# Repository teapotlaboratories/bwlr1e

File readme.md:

# Teapotlabs BWLR1E

Teapotlabs BWLR1E is a solar-powered wireless LoRa environmental sensor capable of sensing temperature, humidity, air pressure and air quality using the on-board BME688. 
With STM32WLE MCU as it's core and AEM10941 for solar charging, the device is capable of multi-year operation with the possibility of indefinite battery-life by utilizing the solar charging capability

Teapotlabs BWLR1E is part of  [Teapot open-hardware project](https://github.com/teapotlaboratories). 
  
## Disclaimer
- The 1KM range is based on [AERQ - Air Quality Monitoring](https://www.seeedstudio.com/blog/2022/04/27/monitoring-indoor-air-pollutants-the-silent-issue-for-smart-city-iot-using-seeed-lora-e5-and-fusion-pcba/) design, but have not been tested on this device yet

## Acknowledgement
The project won't be possible without the amazing work from people across the globe. The following are the reference to those awesome projects:

 - [LoRa e5 Tiny](https://github.com/hallard/LoRa-E5-Tiny)
 - [AERQ - Air Quality Monitoring](https://www.seeedstudio.com/blog/2022/04/27/monitoring-indoor-air-pollutants-the-silent-issue-for-smart-city-iot-using-seeed-lora-e5-and-fusion-pcba/)
	 - [Github](https://github.com/Mircerson/AERQ) 
 - [TSEM](https://hackaday.io/project/159139-tiny-solar-energy-module-tsem)

## Specification

- [RAK3172](https://docs.rakwireless.com/Product-Categories/WisDuo/RAK3172-Module/Overview/): An STM32WLE5CC module
- [AEM10941](https://e-peas.com/product/aem10941): Solar energy harvesting
- 3.3V only power/pin. 
- 3uA Deep-Sleep
- BME688 for Environmental Sensing
- Switchable TX Power. 14 dBm(50mA) or 22 dBm(140mA) ( on 915MHz frequency )
- Supports LoRaWAN 1.0.3
- 1KM+ Range
- UART2 breakout for **Arduino/Mbed OS/STM32Cube** programming 
- SWD breakout for debugging and programming
- iPEX antenna connector 
- 3.7 Volts LiPo Battery

## Schematics

## Boards
 <p align="center">  <br><b>PCB Render</b></p>

Built using KiCAD, the board is design to be as small as possible with all components placed on the top side of the PCB.
The following are the lists of revision of the board:
- Revision 1: Initial design
- Revision 2: Better trace, use rounded trace and change solar cell wiring to parallel for all cell
- Revision 3: Rename 3V3 to PRIMIN and breaks out PRIMIN
- Revision 4: Improve layout and wiring, and add Qwiic connector
- Revision 5: Change C6 to 22uF

The following design are based on the latest revision.
| Top Board | Bottom Board |
|--|--|
|  |  |
|  |  |

 <p align="center"> <br><b>PCB Top and Bottom Layout</b></p> 
  
### Case

Built using [TinkerCAD](https://www.tinkercad.com). The case are 3D printable with any generic 3D printer with/without support. The STL files are available [here](https://github.com/teapotlaboratories/bwlr1e/tree/main/hardware/main/case)
 <p align="center"><br><b>Case Open</b></p>

For adding additional sensors, Qwiic connector is also available on the left side of the board.
 <p align="center"><br><b>Connecting to Adafruit BME688</b></p>

The case is design to be as small as possible with an additional magnets in the back to ease the placement of the sensor. The following are the list of material used at the time of testing:
- 3.7v LiPo Battery, 850mAh 6mm x 30mm x 48mm
- 4 piece of 8mm x 2mm neodymium magnet

<p align="center"><br><b>Sensor Placement with Magnet</b></p>

### Measurement
Power consumption and solar charging current are measured using [Nordic PPK2](https://www.nordicsemi.com/Products/Development-hardware/Power-Profiler-Kit-2)  and [CurrentRanger](https://lowpowerlab.com/shop/product/152).
The following are the summary of the measurement:
- Transmit 14dBm:  305ms @ 20mA
- Deep-Sleep : 3.22 uA
- Direct Sunlight Solar Charge: 9mA
- Indirect Sunlight Solar Charge: 300uA

> :warning: **Tested on Revision 3, but should be similar to Revision 5** 

<p align="center"><br><b>Deep-Sleep</b></p>

<p align="center"><br><b>BME688 Measure and LoRa Transmit</b></p>

| Solar Charge - Direct Sunlight | Solar Charge - Indirect Sunlight |
|--|--|
|  |  |

More measurement can be found [here](https://github.com/teapotlaboratories/bwlr1e/tree/main/docs/measurement)

### Bill Of Materials
Most of the components are generic and can be bought from any electornics/semi-conductor distributor. RAK3172 is the only component available in [RAKwireless store](https://store.rakwireless.com/products/wisduo-lpwan-module-rak3172?variant=40014759493830). The bill of materials can be downloaded [here](https://github.com/teapotlaboratories/bwlr1e/blob/main/hardware/main/bill_of_materials.csv)

> :warning: **Be sure to buy the RAK3172 variant without IPEX to use the On-Board Antenna** 

## Programming

> :warning: **Board can only be powered when LiPo battery is connected** 

Programming the device can be done over the **UART2** or **SWD**, available on the right side of the board or uses the [BWLR1E Programmer](https://github.com/teapotlaboratories/bwlr1e/blob/main/readme_programmer.md).
Out of the factory, the RAK3172 chip ships with an **AT firmware** that can be tested by connecting a USB-to-UART bridge to the **UART2** port.

The following are some very good tutorial to start developing with the device:

- [Communicating with the AT firmware](https://docs.rakwireless.com/Product-Categories/WisDuo/RAK3172-Module/Quickstart/#rak3172-as-a-lora-lorawan-modem-via-at-command)
 - [Programming with Arduino](https://docs.rakwireless.com/Product-Categories/WisDuo/RAK3172-Module/Quickstart/#rak3172-as-a-stand-alone-device-using-rui3)
 - [Programming with STM32Cube](https://docs.rakwireless.com/Product-Categories/WisDuo/RAK3172-Module/Low-Level-Development/#rak3172-on-stm32cubeide-with-stm32wl-sdk-v1-0-0)
 - [Programming with MbedOS](https://github.com/hallard/LoRa-E5-Tiny/blob/main/README.md#compile-and-flash-firmware)

For connecting to the **UART2** port, use any USB-to-UART bridge module. In testing, the [Sparkfun](https://www.sparkfun.com/products/14050) board is used for communication with AT firmware and programming over **Arduino**.
 <p align="center"> <br>Sparkfun USB-to-UART Bridge</p>

> :warning: **Be sure to only use 3.3V module. Do not 5V module** 

### Available SDK
Through **UART2**, user can program the device using the following SDK:
- [Arduino RUI3 SDK](https://github.com/RAKWireless/RAKwireless-Arduino-BSP-Index)
- [Arduino STM32duino SDK](https://github.com/stm32duino/Arduino_Core_STM32)
- [MbedOS](https://github.com/hallard/LoRa-E5-Tiny/blob/main/README.md#compile-and-flash-firmware)
- [STM32Cube](https://docs.rakwireless.com/Product-Categories/WisDuo/RAK3172-Module/Low-Level-Development/#installation-of-stm32cube-ide)

Other than [Arduino RUI3 SDK](https://github.com/RAKWireless/RAKwireless-Arduino-BSP-Index), to program the device, user need to put the device in Serial Bootloader mode by,
1. Press and Hold `BOOT` and `RESET` button
2. Release `RESET` button 
3. Wait few seconds ( try 2 seconds )
4. Release `BOOT` button
5. Device should be in Serial Bootloader mode.

You can also use [STM32CubeProgrammer](https://www.st.com/en/development-tools/stm32cubeprog.html) , instead of the SDK  to upload a firmware
  
### Programming with Teapotlabs BWLR1E Programmer
 <p align="center"> <br>Teapotlabs BWLR1E Programmer</p>

An alternative to solder-free programming is to use the Teapotlabs BWLR1E Programmer. A full detail of the device can be found [here](https://github.com/teapotlaboratories/bwlr1e/blob/main/readme_programmer.md).
The programmer connects to UART2 of the device. 

## License
The product is open-source! However, some part of library used under **src**, might have it's own license.
Please reach out or create a ticket to report any license violation.

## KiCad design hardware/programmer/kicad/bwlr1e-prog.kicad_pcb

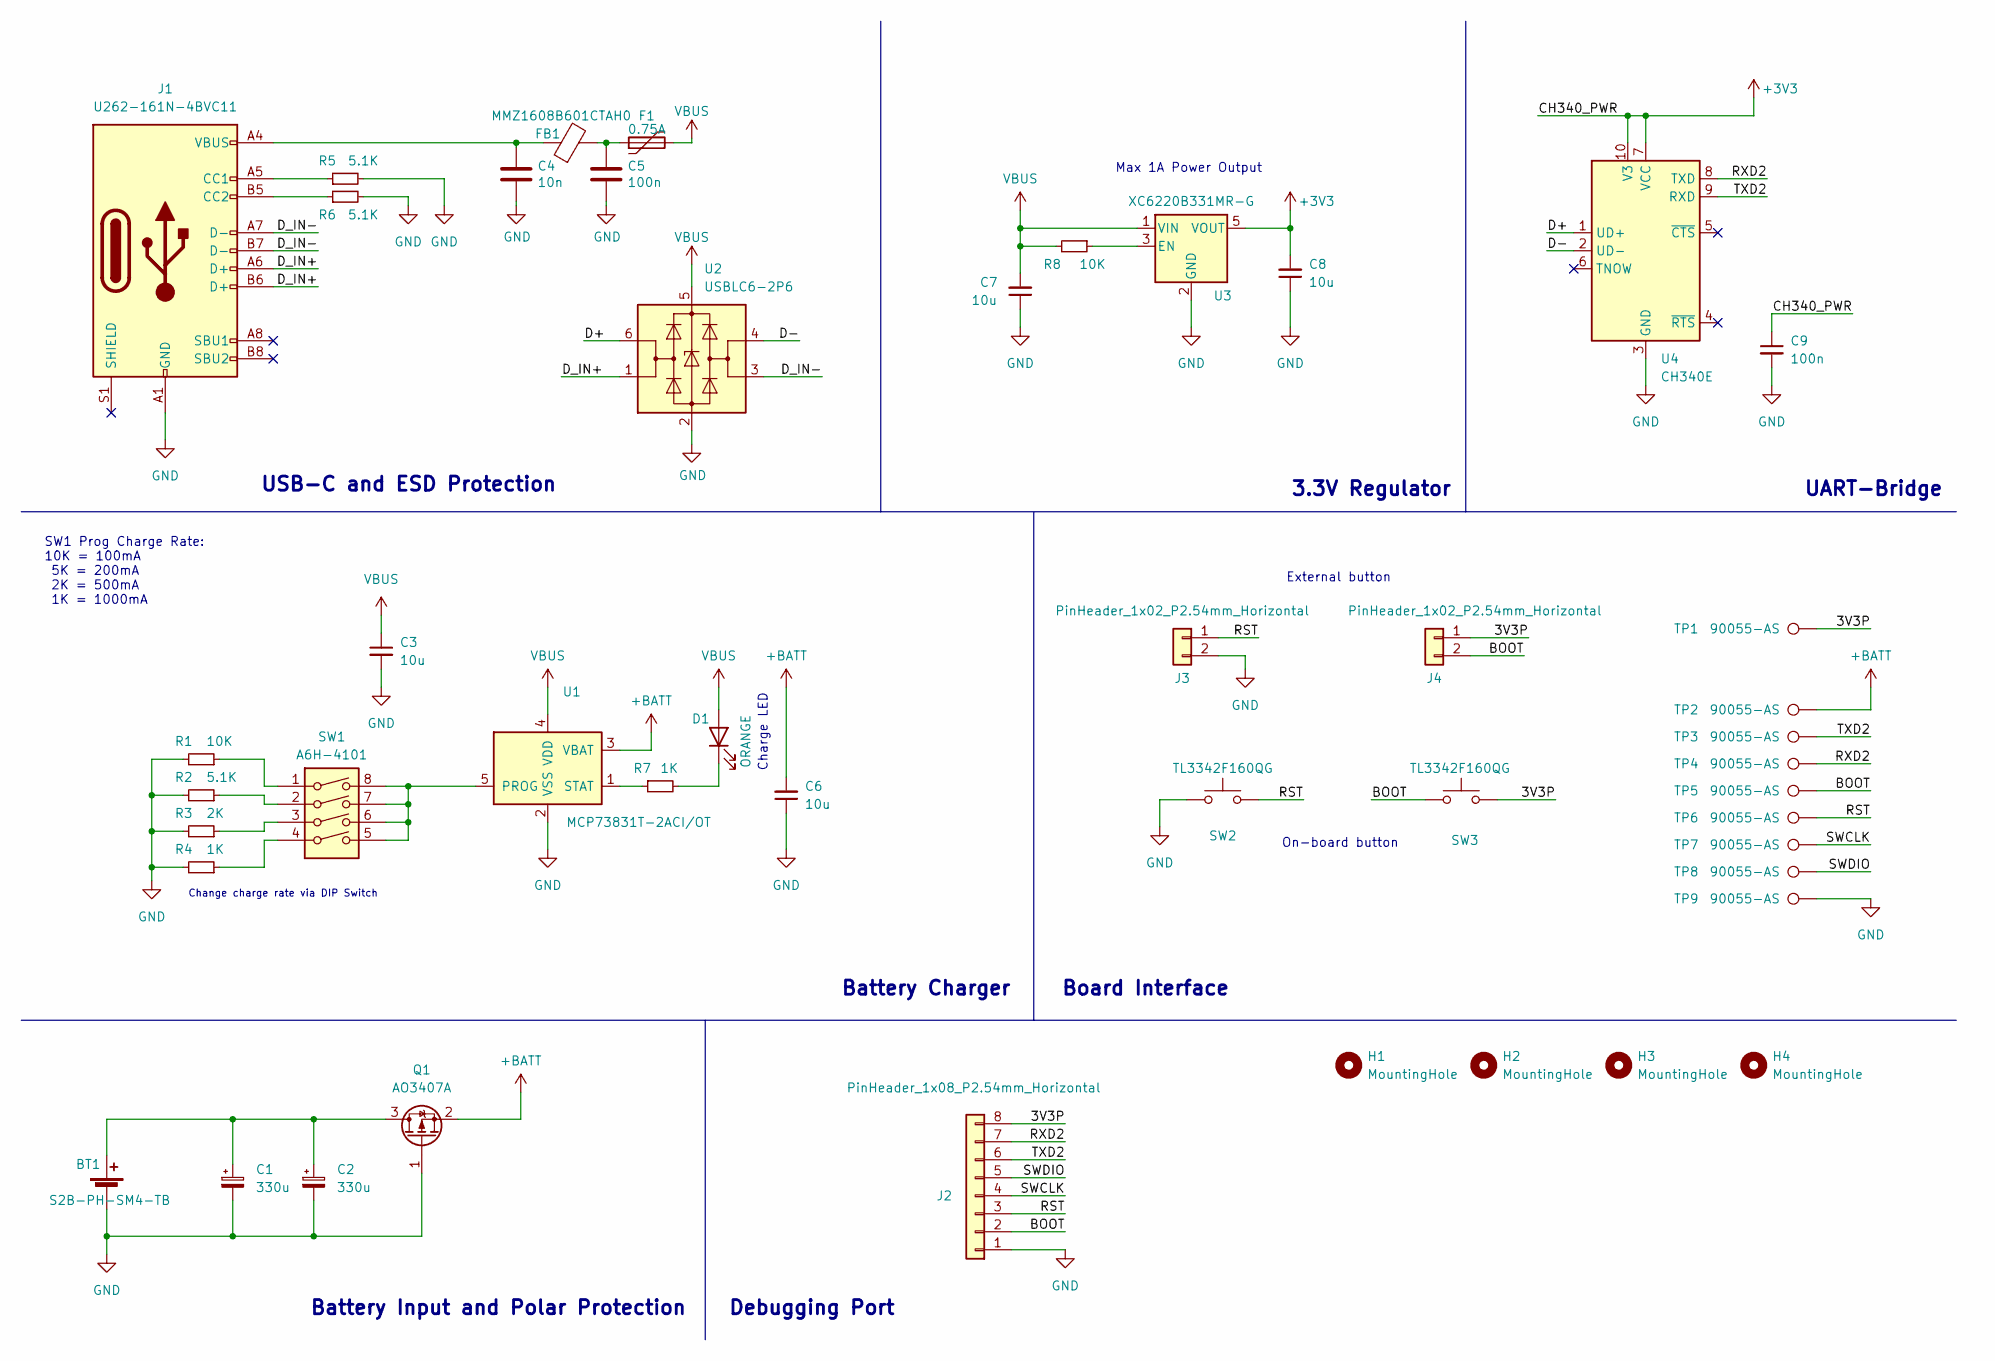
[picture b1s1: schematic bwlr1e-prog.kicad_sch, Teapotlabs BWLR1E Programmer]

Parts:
BT1: S2B-PH-SM4-TB; JST_PH_S2B-PH-SM4-TB_1x02-1MP_P2.00mm_Horizontal; Part Number S2B-PH-SM4-TB
C1, C2: 330u; CP_EIA-3528-15_AVX-H; Part Number T520B337M006ATE040
C3: 10u; C_0603_1608Metric; Part Description Ceramic Capacitor 10uF 10% 10V X5R
C4: 10n; C_0402_1005Metric; Part Number CC0402KRX7R9BB103
C5: 100n; C_0402_1005Metric; Part Number CC0402KRX5R6BB104
C6, C7, C8: 10u; C_0805_2012Metric; Part Description Ceramic Capacitor 10uF 10% 10V X5R
C9: 100n; C_0603_1608Metric; Part Description Ceramic Capacitor 100nF 10% 10V X7R
D1: ORANGE; LED_0603_1608Metric; Part Description Orange 2V 25mA
F1: 0.75A; Fuse_0805_2012Metric; Part Number SMD0805P075TF
FB1: MMZ1608B601CTAH0; L_0603_1608Metric; Part Number MMZ1608B601CTAH0
H1, H2, H3, H4: MountingHole; MountingHole_2.2mm_M2
J1: U262-161N-4BVC11; USB_C_Receptacle_XKB_U262-16XN-4BVC11; Part Number U262-161N-4BVC11
J2: PinHeader_1x08_P2.54mm_Horizontal
J3, J4: PinHeader_1x02_P2.54mm_Horizontal
Q1: AO3407A; SOT-23; Part Number AO3407A
R1: 10K; R_0603_1608Metric; Part Description Resistor 10K 1% 100mW
R2: 5.1K; R_0603_1608Metric; Part Description Resistor 5.1K 1% 100mW
R3: 2K; R_0603_1608Metric; Part Description Resistor 2K 1% 100mW
R4: 1K; R_0603_1608Metric; Part Description Resistor 1K 1% 100mW
R5, R6: 5.1K; R_0402_1005Metric; Part Description Resistor 5.1K 1% 62.5mW
R7: 1K; R_0603_1608Metric; Part Description Resistor 1k 5% 100mW
R8: 10K; R_0603_1608Metric; Part Description Resistor 10k 5% 100mW
SW1: A6H-4101; SW_DIP_SPSTx04_Slide_Omron_A6H-4101_W6.15mm_P1.27mm; Part Number A6H-4101
SW2, SW3: TL3342F160QG; SW_SPST_TL3342; Part Number TL3342F160QG
TP1, TP2, TP3, TP4, TP5, TP6, TP7, TP8, TP9: 90055-AS; Part Number 90055-AS
U1: MCP73831T-2ACI/OT; SOT-23-5; Part Number MCP73831T-2ACI/OT
U2: USBLC6-2P6; SOT-666; Part Number USBLC6-2P6
U3: XC6220B331MR-G; SOT-23-5; Part Number XC6220B331MR-G
U4: CH340E; MSOP-10_3x3mm_P0.5mm; Part Number CH340E

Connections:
+3V3: C8.2, C9.1, U3.5 (VOUT), U4.7 (VCC), U4.10 (V3)
+BATT: C6.2, Q1.2 (S), TP2.1, U1.3 (VBAT)
/3V3P: J2.8, J4.1, SW3.2, TP1.1
/BOOT: J2.2, J4.2, SW3.1, TP5.1
/D+: U2.6 (I/O1), U4.1 (UD+)
/D-: U2.4 (I/O2), U4.2 (UD-)
/D_IN+: J1.A6 (D+), J1.B6 (D+), U2.1 (I/O1)
/D_IN-: J1.A7 (D-), J1.B7 (D-), U2.3 (I/O2)
/RST: J2.3, J3.1, SW2.2, TP6.1
/RXD2: J2.7, TP4.1, U4.8 (TXD)
/SWCLK: J2.4, TP7.1
/SWDIO: J2.5, TP8.1
/TXD2: J2.6, TP3.1, U4.9 (RXD)
GND: BT1.2 (-), C1.2, C2.2, C3.2, C4.2, C5.2, C6.1, C7.1, C8.1, C9.2, J1.A1 (GND), J1.A12 (GND), J1.B1 (GND), J1.B12 (GND), J2.1, J3.2, Q1.1 (G), R1.2, R2.2, R3.2, R4.2, R5.2, R6.2, SW2.1, TP9.1, U1.2 (VSS), U2.2 (GND), U3.2 (GND), U4.3 (GND)
unnamed: BT1.1 (+), C1.1, C2.1, Q1.3 (D)
unnamed: C4.1, FB1.1, J1.A4 (VBUS), J1.A9 (VBUS), J1.B4 (VBUS), J1.B9 (VBUS)
unnamed: C5.1, F1.1, FB1.2
unnamed: D1.1 (K), R7.2
unnamed: J1.A5 (CC1), R5.1
unnamed: J1.B5 (CC2), R6.1
unnamed: R1.1, SW1.1
unnamed: R2.1, SW1.2
unnamed: R3.1, SW1.3
unnamed: R4.1, SW1.4
unnamed: SW1.5, SW1.6, SW1.7, SW1.8, U1.5 (PROG)
unnamed: R7.1, U1.1 (STAT)
unnamed: R8.1, U3.3 (EN)
VBUS: C3.1, C7.2, D1.2 (A), F1.2, R8.2, U1.4 (VDD), U2.5 (VBUS), U3.1 (VIN)

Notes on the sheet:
SW1 Prog Charge Rate: 10K = 100mA 5K = 200mA 2K = 500mA 1K = 1000mA
External button
Max 1A Power Output
On-board button
Debugging Port
Charge LED
UART-Bridge
Change charge rate via DIP Switch
Battery Input and Polar Protection
USB-C and ESD Protection
Battery Charger
3.3V Regulator
Board Interface

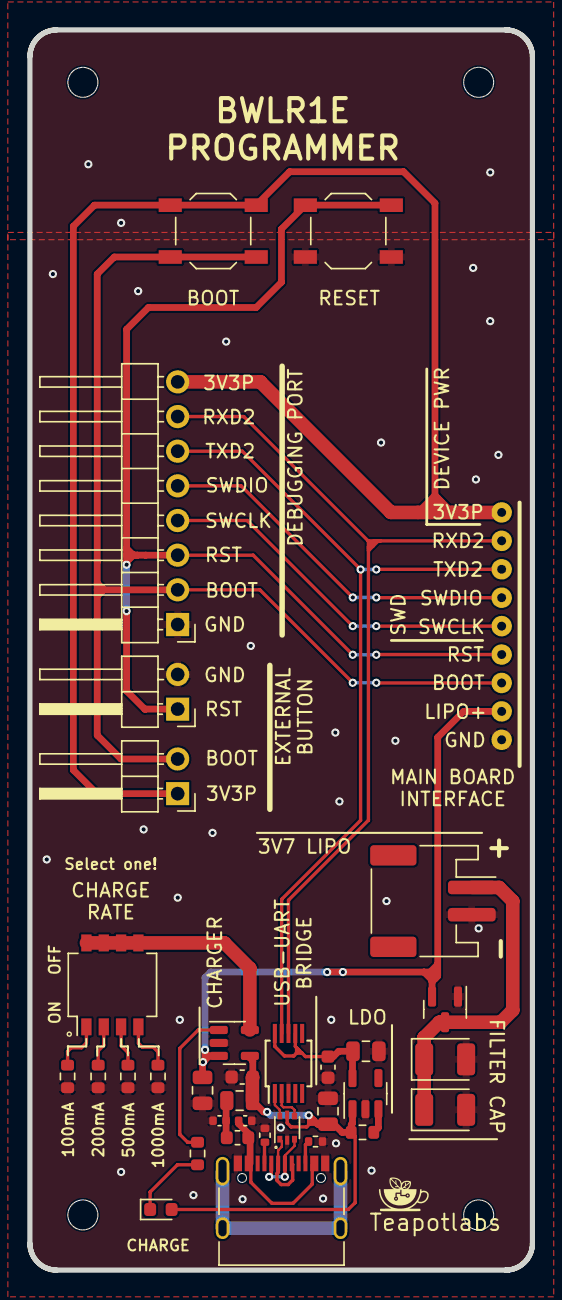
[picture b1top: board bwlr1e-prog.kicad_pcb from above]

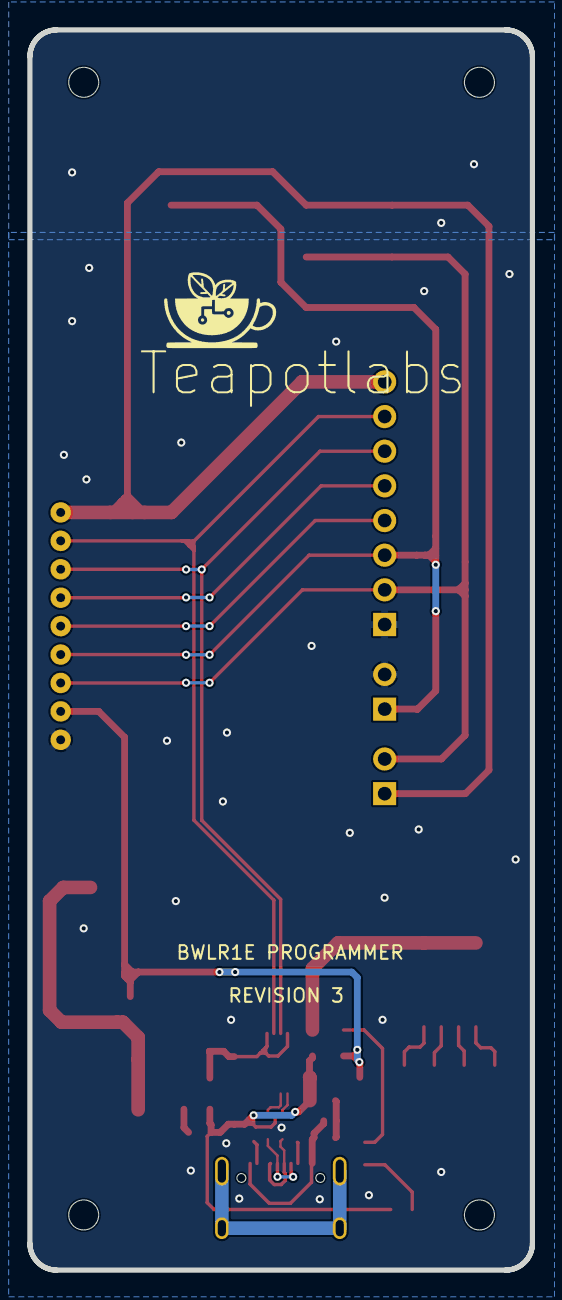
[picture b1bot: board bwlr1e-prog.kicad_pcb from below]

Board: 2 copper layers, 36.8 x 90.9 mm, 46 parts (9 on the bottom side), 28 nets.

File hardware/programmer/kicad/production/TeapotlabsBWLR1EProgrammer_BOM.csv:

Id,Designator,Quantity,Manufacturer,Manufacturer Part Number,Value,Description,Footprint,Type,Distributor,Distributor Part Number,Distributor Link
1,BT1,1,JST,S2B-PH-SM4-TB(LF)(SN),S2B-PH-SM4-TB(LF)(SN),"Connector Header Right Angle 2 position 0.079"" (2.00mm)",JST_PH_S2B-PH-SM4-TB,SMD,LCSC,C295747,https://www.lcsc.com/product-detail/Wire-To-Board-Wire-To-Wi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
2,"C1, C2",2,KEMET,T520B337M006ATE040,330u,Tantalum Capacitors 330µF 20% 6.3 V 40mOhm,CP_EIA-3528-15_AVX-H,SMD,LCSC,C696806,https://www.lcsc.com/product-detail/span-style-background-co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
3,C3,1,Samsung Electro-Mechanics,CL10A106KP8NNNC,10u,Ceramic Capacitor 10uF 10% 10V X5R,0603_1608Metric,SMD,LCSC,C19702,https://www.lcsc.com/product-detail/_Samsung-Electro-Mechani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
4,C4,1,YAGEO,CC0402KRX7R9BB103,10n,Ceramic Capacitor 10nF 10% 50V X7R,0402_1005Metric,SMD,LCSC,C60133,https://www.lcsc.com/product-detail/Multilayer-Ceramic-Capac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
5,C5,1,YAGEO,CC0402KRX5R6BB104,100n,Ceramic Capacitor 100nF 10% 10V X5R,0402_1005Metric,SMD,LCSC,C129131,https://www.lcsc.com/product-detail/Multilayer-Ceramic-Capac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
6,"C6, C7, C8",3,Samsung Electro-Mechanics,CL21A106KPFNNNE,10u,Ceramic Capacitor 10uF 10% 10V X5R,0805_2012Metric,SMD,LCSC,C17024,https://www.lcsc.com/product-detail/_Samsung-Electro-Mechani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
7,C9,1,YAGEO,CC0603KRX7R6BB104,100n,Ceramic Capacitor 100nF 10% 10V X7R,0603_1608Metric,SMD,LCSC,C519438,https://www.lcsc.com/product-detail/_YAGEO-_C519438.html
8,D1,1,EKINGLUX,E6C0603SEAC1UDA,ORANGE,LED Orange 2V 25mA,0603_1608Metric,SMD,LCSC,C375450,https://www.lcsc.com/product-detail/_EKINGLUX-_C375450.html
9,F1,1,RUILON,SMD0805P075TF,0.75A,Resettable Fuses 6V 750mA 40A 1.5A,0805_2012Metric,SMD,LCSC,C20979,https://www.lcsc.com/product-detail/Resettable-Fuses_RUILON-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
10,FB1,1,TDK,MMZ1608B601CTAH0,MMZ1608B601CTAH0,Ferrite Beads 400mΩ ±25% 600Ω@100MHz,0603_1608Metric,SMD,LCSC,C97120,https://www.lcsc.com/product-detail/Ferrite-Beads_TDK-MMZ160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
12,J1,1,XKB Connectivity,U262-161N-4BVC11,U262-161N-4BVC11,USB-C Receptacle,XKB_U262-16XN-4BVC11,SMD,LCSC,C319148,https://www.lcsc.com/product-detail/USB-Connectors_XKB-Conne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
13,J2,1,HCTL,PZ254-1-08-W-8.5,PinHeader_1x08_P2.54mm_Horizontal,PinHeader 1x08 Pitch 2.54mm Horizontal,PinHeader_1x08_P2.54mm_Horizontal,THT,LCSC,C2894950,https://www.lcsc.com/product-detail/span-style-background-co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
14,"J3, J4",2,XFCN,PZ254R-11-02P,PinHeader_1x02_P2.54mm_Horizontal,PinHeader 1x02 Pitch 2.54mm Horizontal,PinHeader_1x02_P2.54mm_Horizontal,THT,LCSC,C492410,https://www.lcsc.com/product-detail/span-style-background-co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
15,Q1,1,Alpha & Omega Semicon,AO3407A,AO3407A,"MOSFET P Channel 30V 4.3A 48mΩ@10V,4.3A 1.4W",SOT-23,SMD,LCSC,C15155,https://www.lcsc.com/product-detail/MOSFETs_Alpha-Omega-Semi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
16,"R1, R8",2,UNI-ROYAL(Uniroyal Elec),0603WAF1002T5E,10K,Resistor 10K 1% 100mW,0603_1608Metric,SMD,LCSC,C25804,https://www.lcsc.com/product-detail/Chip-span-style-backgrou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
17,R2,1,UNI-ROYAL(Uniroyal Elec),0603WAF5101T5E,5.1K,Resistor 5.1K 1% 100mW,0603_1608Metric,SMD,LCSC,C23186,https://www.lcsc.com/product-detail/Chip-span-style-backgrou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
18,R3,1,UNI-ROYAL(Uniroyal Elec),0603WAF2001T5E,2K,Resistor 2K 1% 100mW,0603_1608Metric,SMD,LCSC,C22975,https://www.lcsc.com/product-detail/Chip-span-style-backgrou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
19,"R4, R7",2,UNI-ROYAL(Uniroyal Elec),0603WAF1001T5E,1K,Resistor 1K 1% 100mW,0603_1608Metric,SMD,LCSC,C21190,https://www.lcsc.com/product-detail/Chip-span-style-backgrou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
20,"R5, R6",2,UNI-ROYAL(Uniroyal Elec),0402WGF5101TCE,5.1K,Resistor 5.1K 1% 100mW,0402_1005Metric,SMD,LCSC,C25905,https://www.lcsc.com/product-detail/Chip-span-style-backgrou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
21,SW1,1,Omron,A6H-4101,A6H-4101,DIP Switches SMD 4Bit SPST 24V 25mA,A6H-4101,SMD,LCSC,C397291,https://www.lcsc.com/product-detail/DIP-Switches_Omron-Elect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
22,"SW2, SW3",2,E-Switch,TL3342F160QG,TL3342F160QG,SPST SMD NO 50mA 100MΩ 100000 Times 12V 160gf@±50gf,SW_SPST_TL3342,SMD,LCSC,C2886898,https://www.lcsc.com/product-detail/Tactile-Switches_E-Switc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
23,"TP1, TP2, TP3, TP4, TP5, TP6, TP7, TP8, TP9",9,Preci-Dip,90055-AS,90055-AS,Contact Spring Loaded SMD Gold,90055-AS,THT,Digikey,1212-1855-ND,https://www.digikey.com/en/products/detail/preci-dip/90055-A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
24,U1,1,Microchip,MCP73831T-2ACI/OT,MCP73831T-2ACI/OT, Battery Management ICs 1.5A,SOT-23-5,SMD,LCSC,C424093,https://www.lcsc.com/product-detail/Battery-Management-ICs_M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
25,U2,1,STMicroelectronics,USBLC6-2P6,USBLC6-2P6, ESD Protection Devices 6V 17V Unidirectional 5.25V,SOT-666,SMD,LCSC,C15999,https://www.lcsc.com/product-detail/ESD-Protection-Devices_S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
26,U3,1,Torex Semiconductor,XC6220B331MR-G,XC6220B331MR-G,Linear Voltage Regulators (LDO) 1000mA Fixed +3.3V,SOT-23-5,SMD,LCSC,C86534,https://www.lcsc.com/product-detail/Linear-Voltage-Regulator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
27,U4,1,WCH,CH340E,CH340E,USB-UART Bridge 2Mbps Transceiver USB 2.0,MSOP-10_3x3mm_P0.5mm,SMD,LCSC,C99652,https://www.lcsc.com/product-detail/USB-ICs_WCH-Jiangsu-Qin-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

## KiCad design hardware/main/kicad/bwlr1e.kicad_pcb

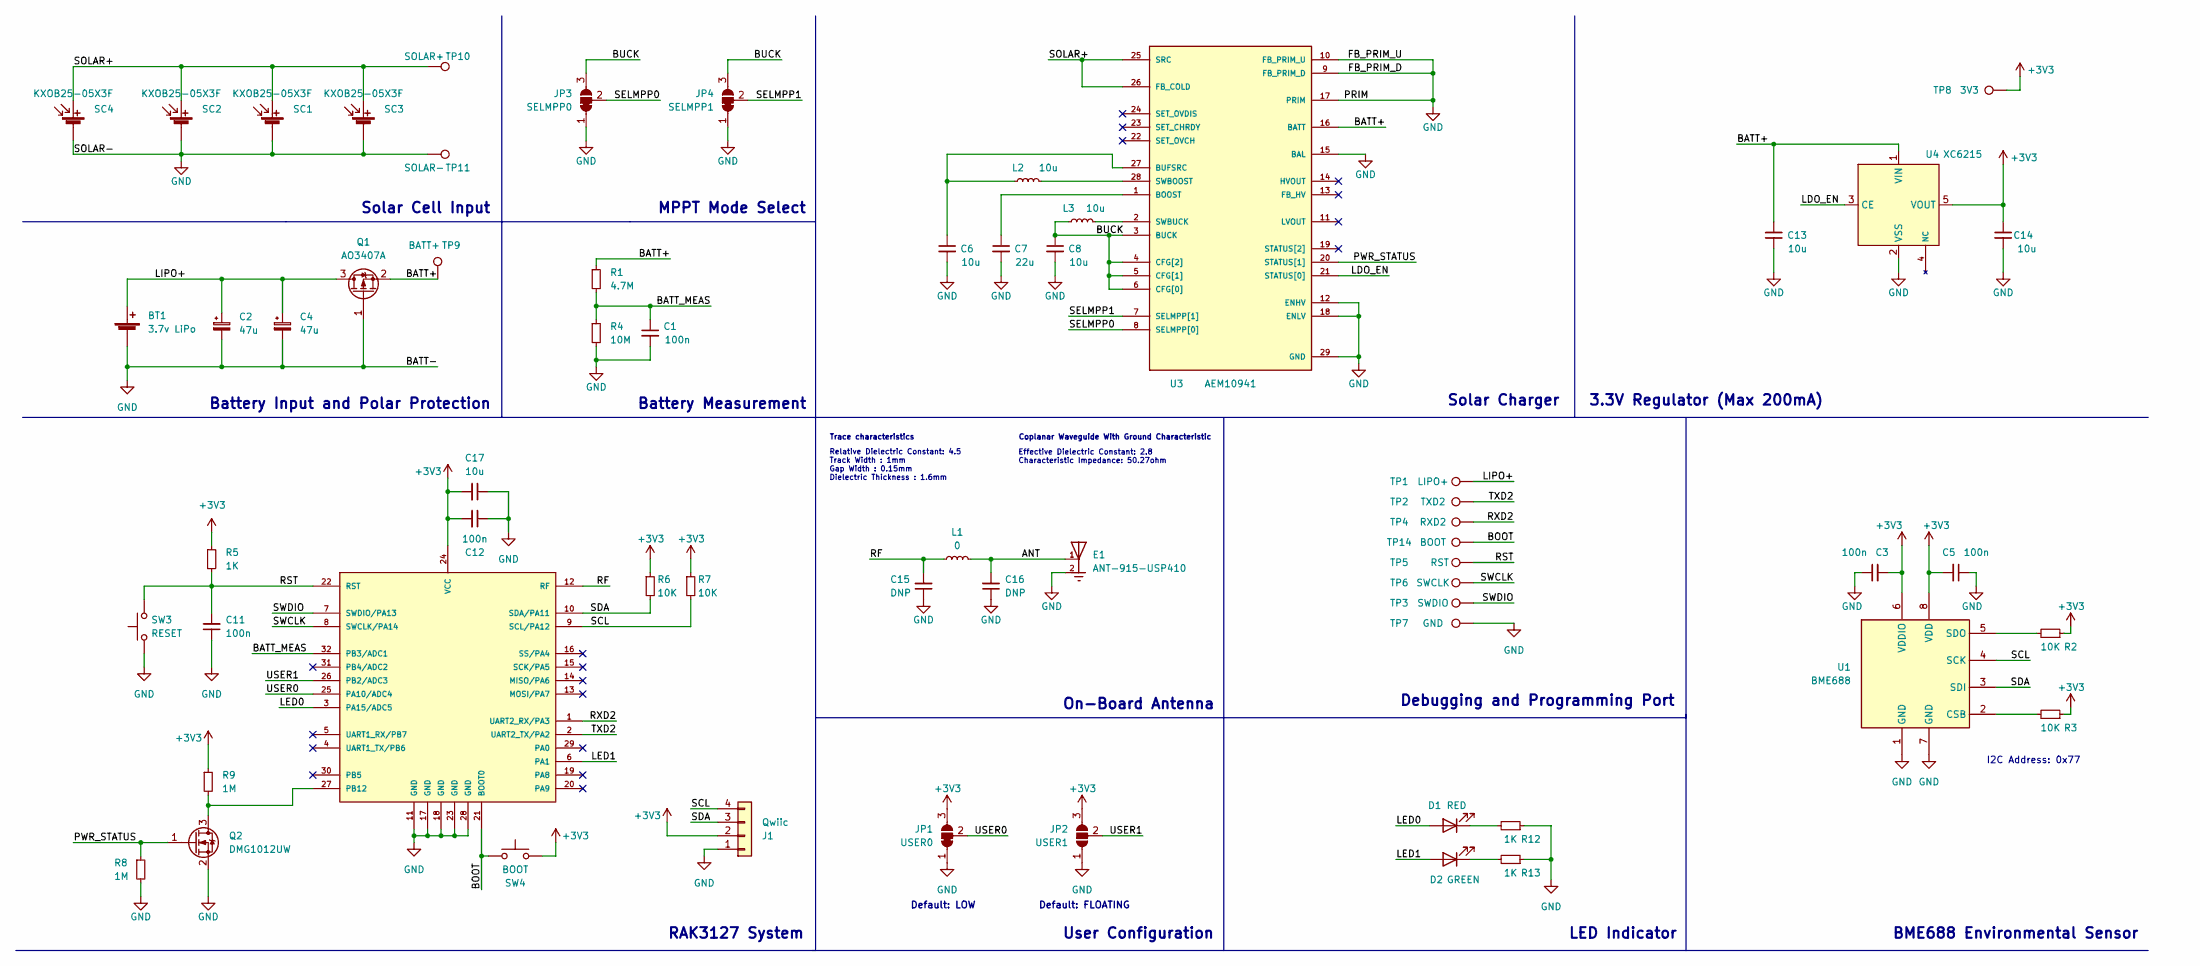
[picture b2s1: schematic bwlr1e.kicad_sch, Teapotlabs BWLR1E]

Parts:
BT1: 3.7v LiPo; JST_PH_S2B-PH-SM4-TB_1x02-1MP_P2.00mm_Horizontal; Part Number S2B-PH-SM4-TB
C1, C3, C5, C11, C12: 100n; C_0603_1608Metric_Pad1.08x0.95mm_HandSolder; Part Description Ceramic Capacitor 100nF 10% 10V X7R
C2, C4: 47u; CP_EIA-3528-15_AVX-H_Pad1.50x2.35mm_HandSolder; Part Number TPSB476K010R0350
C6: 10u; C_0603_1608Metric; Part Description Ceramic Capacitor 10uF 10% 10V X5R
C7: 22u; C_0603_1608Metric_Pad1.08x0.95mm_HandSolder; Part Description Ceramic Capacitor 22uF 20% 10V X5R
C8, C13, C14, C17: 10u; C_0603_1608Metric_Pad1.08x0.95mm_HandSolder; Part Description Ceramic Capacitor 10uF 10% 10V X5R
C15, C16: DNP; C_0603_1608Metric_Pad1.08x0.95mm_HandSolder
D1: RED; LED_0603_1608Metric_Pad1.05x0.95mm_HandSolder; Part Description Red 2V 20mA
D2: GREEN; LED_0603_1608Metric_Pad1.05x0.95mm_HandSolder; Part Description Green 2V 20mA
E1: ANT-915-USP410; XDCR_ANT-915-USP410; Part Number ANT-915-USP410
J1: Qwiic; JST_SH_SM04B-SRSS-TB_1x04-1MP_P1.00mm_Horizontal; Part Number SM04B-SRSS-TB
JP1: USER0; SolderJumper-3_P1.3mm_Bridged12_RoundedPad1.0x1.5mm
JP2: USER1; SolderJumper-3_P1.3mm_Open_RoundedPad1.0x1.5mm
JP3: SELMPP0; SolderJumper-3_P1.3mm_Bridged12_RoundedPad1.0x1.5mm_NumberL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
JP4: SELMPP1; SolderJumper-3_P1.3mm_Bridged12_RoundedPad1.0x1.5mm_NumberL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
L1: 0; L_0603_1608Metric_Pad1.05x0.95mm_HandSolder
L2: 10u; IND_LPS4012-103MRB; Part Description Power Inductor 10uH 20% 1.1A
L3: 10u; L_0603_1608Metric_Pad1.05x0.95mm_HandSolder; Part Description Power Inductor 10uH 20% 90mA
Q1: AO3407A; SOT-23; Part Number AO3407A
Q2: DMG1012UW; SOT-323_SC-70; Part Number DMG1012UW
R1: 4.7M; R_0603_1608Metric_Pad0.98x0.95mm_HandSolder; Part Description Resistor 4.7M 1% 100mW
R2, R3, R6, R7: 10K; R_0603_1608Metric_Pad0.98x0.95mm_HandSolder; Part Description Resistor 10K 5% 100mW
R4: 10M; R_0603_1608Metric_Pad0.98x0.95mm_HandSolder; Part Description Resistor 10M 1% 100mW
R5, R12, R13: 1K; R_0603_1608Metric_Pad0.98x0.95mm_HandSolder; Part Description Resistor 1K 5% 100mW
R8, R9: 1M; R_0603_1608Metric_Pad0.98x0.95mm_HandSolder; Part Description Resistor 1M 5% 100mW
SC1, SC2, SC3, SC4: KXOB25-05X3F; Part Number KXOB25-05X3F
SW3: RESET; SW_SPST_TL3342; Part Number TL3342F160QG
SW4: BOOT; SW_SPST_TL3342; Part Number TL3342F160QG
TP1: LIPO+; TestPoint_Pad_D1.0mm
TP2: TXD2; TestPoint_Pad_D1.0mm
TP3: SWDIO; TestPoint_Pad_D1.0mm
TP4: RXD2; TestPoint_Pad_D1.0mm
TP5: RST; TestPoint_Pad_D1.0mm
TP6: SWCLK; TestPoint_Pad_D1.0mm
TP7: GND; TestPoint_Pad_D1.0mm
TP8: 3V3; TestPoint_Pad_D1.0mm
TP9: BATT+; TestPoint_Pad_D1.0mm
TP10: SOLAR+; TestPoint_Pad_D1.5mm
TP11: SOLAR-; TestPoint_Pad_D1.5mm
TP14: BOOT; TestPoint_Pad_D1.0mm
U1: BME688; BME680-PSON80P300X300X100-8N; Part Number BME688
U2: RAK3172-T; RAK3172; Part Number 309054
U3: AEM10941; QFN-28-1EP_5x5mm_P0.5mm_EP3.35x3.35mm; Part Number AEM10941-QFN
U4: XC6215; SOT-23-5; Part Number XC6215B332MR-G

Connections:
+3V3: C3.2, C5.2, C12.2, C14.1, C17.2, J1.2, JP1.3 (B), JP2.3 (B), R2.1, R3.1, R5.1, R6.1, R7.1, R9.1, SW4.2, TP8.1, U1.6 (VDDIO), U1.8 (VDD), U2.24 (VCC), U4.5 (VOUT)
/ANT: C16.2, E1.1, L1.2
/BATT+: C13.1, Q1.2 (S), R1.1, TP9.1, U3.16 (BATT), U4.1 (VIN)
/BATT_MEAS: C1.1, R1.2, R4.1, U2.32 (PB3/ADC1)
/BOOT: SW4.1, TP14.1, U2.21 (BOOT0)
/BUCK: C8.1, JP3.3 (B), JP4.3 (B), L3.1, U3.3 (BUCK), U3.4 (CFG[2]), U3.5 (CFG[1]), U3.6 (CFG[0])
/LDO_EN: U3.21 (STATUS[0]), U4.3 (CE)
/LED0: D1.2 (A), U2.3 (PA15/ADC5)
/LED1: D2.2 (A), U2.6 (PA1)
/LIPO+: BT1.1 (+), C2.1, C4.1, Q1.3 (D), TP1.1
/PWR_STATUS: Q2.1 (G), R8.1, U3.20 (STATUS[1])
/RF: C15.2, L1.1, U2.12 (RF)
/RST: C11.2, R5.2, SW3.2, TP5.1, U2.22 (RST)
/RXD2: TP4.1, U2.1 (UART2_RX/PA3)
/SCL: J1.4, R7.2, U1.4 (SCK), U2.9 (SCL/PA12)
/SDA: J1.3, R6.2, U1.3 (SDI), U2.10 (SDA/PA11)
/SELMPP0: JP3.2 (C), U3.8 (SELMPP[0])
/SELMPP1: JP4.2 (C), U3.7 (SELMPP[1])
/SOLAR+: SC1.1 (+), SC2.1 (+), SC3.1 (+), SC4.1 (+), TP10.1, U3.25 (SRC), U3.26 (FB_COLD)
/SWCLK: TP6.1, U2.8 (SWCLK/PA14)
/SWDIO: TP3.1, U2.7 (SWDIO/PA13)
/TXD2: TP2.1, U2.2 (UART2_TX/PA2)
/USER0: JP1.2 (C), U2.25 (PA10/ADC4)
/USER1: JP2.2 (C), U2.26 (PB2/ADC3)
GND: BT1.2 (-), C1.2, C2.2, C3.1, C4.2, C5.1, C6.2, C7.2, C8.2, C11.1, C12.1, C13.2, C14.2, C15.1, C16.1, C17.1, E1.2, J1.1, JP1.1 (A), JP2.1 (A), JP3.1 (A), JP4.1 (A), Q1.1 (G), Q2.2 (S), R4.2, R8.2, R12.1, R13.1, SC1.2 (-), SC2.2 (-), SC3.2 (-), SC4.2 (-), SW3.1, TP7.1, TP11.1, U1.1 (GND), U1.7 (GND), U2.11 (GND), U2.17 (GND), U2.18 (GND), U2.23 (GND), U2.28 (GND), U3.9 (FB_PRIM_D), U3.10 (FB_PRIM_U), U3.12 (ENHV), U3.15 (BAL), U3.17 (PRIM), U3.18 (ENLV), U3.29 (GND), U4.2 (VSS)
unnamed: D1.1 (K), R12.2
unnamed: D2.1 (K), R13.2
unnamed: Q2.3 (D), R9.2, U2.27 (PB12)
unnamed: R3.2, U1.2 (CSB)
unnamed: R2.2, U1.5 (SDO)
unnamed: C7.1, U3.1 (BOOST)
unnamed: C6.1, L2.1, U3.27 (BUFSRC)
unnamed: L2.2, U3.28 (SWBOOST)
unnamed: L3.2, U3.2 (SWBUCK)

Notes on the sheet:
On-Board Antenna
Effective Dielectric Constant: 2.8 Characteristic Impedance: 50.27ohm
RAK3127 System
MPPT Mode Select
BME688 Environmental Sensor
LED Indicator
Coplanar Waveguide With Ground Characteristic
Solar Cell Input
Solar Charger
Default: FLOATING
Default: LOW
Battery Measurement
Trace characteristics
I2C Address: 0x77
Battery Input and Polar Protection
User Configuration
3.3V Regulator (Max 200mA)
Relative Dielectric Constant: 4.5 Track Width : 1mm Gap Width : 0.15mm Dielectric Thickness : 1.6mm
Debugging and Programming Port

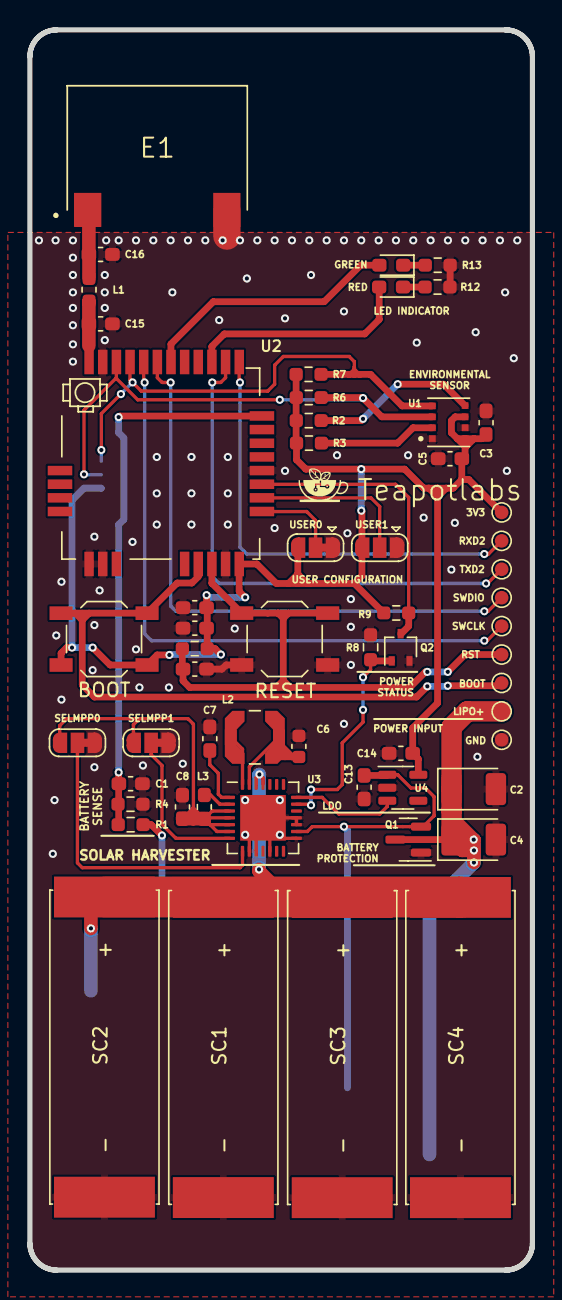
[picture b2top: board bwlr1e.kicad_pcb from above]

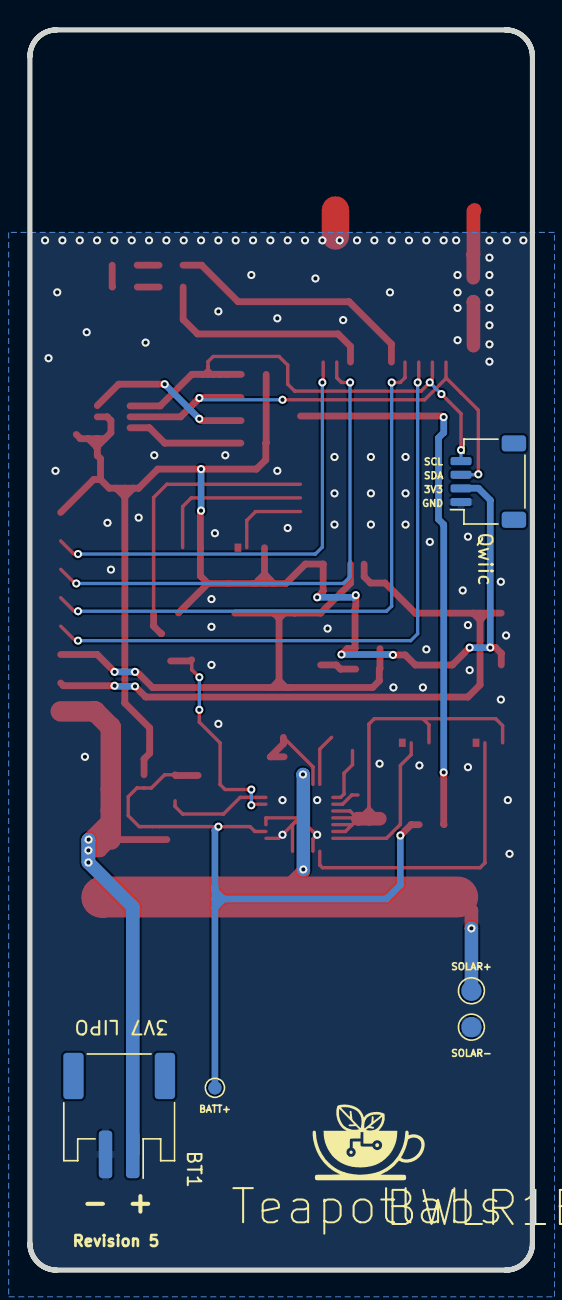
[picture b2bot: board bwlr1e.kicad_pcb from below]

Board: 2 copper layers, 36.8 x 90.9 mm, 62 parts (5 on the bottom side), 34 nets.

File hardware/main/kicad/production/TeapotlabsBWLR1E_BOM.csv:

Id,Designator,Quantity,Manufacturer,Manufacturer Part Number,Value,Description,Footprint,Type,Distributor,Distributor Part Number,Distributor Link
1,BT1,1,JST,S2B-PH-SM4-TB,3.7v LiPo,"Connector Header Right Angle 2 position 0.079"" (2.00mm)",JST_PH_S2B-PH-SM4-TB,SMD,LCSC,C295747,https://www.lcsc.com/product-detail/Wire-To-Board-Wire-To-Wi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
2,"C1, C3, C5, C11, C12",5,YAGEO,CC0603KRX7R6BB104,100n,Ceramic Capacitor 100nF 10% 10V X7R,C_0603_1608Metric,SMD,LCSC,C519438,https://www.lcsc.com/product-detail/Multilayer-Ceramic-Capac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
3,"C2, C4",2,KYOCERA AVX,TPSB476K010R0350,47u,Tantalum Capacitors 47µF 10% 10 V 250mOhm,EIA-3528-15,SMD,Digikey,478-9088-1-ND,https://www.digikey.com/en/products/detail/kyocera-avx/TPSB4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
4,C7,1,Murata Electronics,GRM188R61A226ME15D,22u,Ceramic Capacitor 22uF 20% 10V X5R,C_0603_1608Metric,SMD,LCSC,C84419,https://www.lcsc.com/product-detail/Multilayer-Ceramic-Capac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
5,"C6, C8, C13, C14, C17",5,Murata Electronics,GRT188R61A106KE13D,10u,Ceramic Capacitor 10uF 10% 10V X5R,C_0603_1608Metric,SMD,LCSC,C782172,https://www.lcsc.com/product-detail/Multilayer-Ceramic-Capac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
6,D1,1,Lite-On,LTST-C191KRKT,RED,Red 2V 20mA,LED_0603_1608Metric,SMD,LCSC,C125099,https://www.lcsc.com/product-detail/Light-Emitting-Diodes-LE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
7,D2,1,Lite-On,LTST-C190KGKT,GREEN,Green 2V 20mA,LED_0603_1608Metric,SMD,LCSC,C125094,https://www.lcsc.com/product-detail/Light-Emitting-Diodes-LE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
8,E1,1,Linx Technologies Inc.,ANT-915-USP410,ANT-915-USP410,Chip RF Antenna 902MHz ~ 930MHz 0.9dBi Solder Surface Mount,ANT-915-USP410,SMD,Digikey,343-ANT-915-USP410CT-ND,https://www.digikey.com/en/products/detail/linx-technologies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
9,J1,1,JST,SM04B-SRSS-TB,Qwiic,"Connector Header Right Angle 4 position 0.039"" (1.00mm)",JST_SH_SM04B-SRSS-TB,SMD,LCSC,C160404,https://www.lcsc.com/product-detail/Wire-To-Board-Wire-To-Wi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
10,L1,1,UNI-ROYAL(Uniroyal Elec),0603WAF0000T5E,0,Resistor 0 5% 100mW,L_0603_1608Metric,SMD,LCSC,C21189,https://www.lcsc.com/product-detail/Chip-Resistor-Surface-Mo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
11,L2,1,Coilcraft,LPS4012-103MRC,10u,Power Inductor 10uH 20% 1.1A,IND_LPS4012-103MRB,SMD,Mouser,994-LPS4012-103MRC,https://www.mouser.com/ProductDetail/994-LPS4012-103MRC
12,L3,1,TDK,MLZ1608M100WT000,10u,Power Inductor 10uH 20% 90mA,L_0603_1608Metric,SMD,LCSC,C76798,https://www.lcsc.com/product-detail/Inductors-SMD_TDK-MLZ160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
13,Q1,1,Alpha & Omega Semicon,AO3407A,AO3407A,P-Channel Enhacnement Mode MOSFET 30V 4.3A 48mΩ@10V,SOT-23,SMD,LCSC,C15155,https://www.lcsc.com/product-detail/MOSFETs_Alpha-Omega-Semi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
14,Q2,1,TECH PUBLIC,DMG1012UW,DMG1012UW,N-Channel Enhancement Mode MOSFET 20V 0.9A 300mΩ@2.5V,SOT-323_SC-70,SMD,LCSC,C2940609,https://www.lcsc.com/product-detail/MOSFETs_TECH-PUBLIC-DMG1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
15,R1,1,UNI-ROYAL(Uniroyal Elec),0603WAF4704T5E,4.7M,Resistor 4.7M 1% 100mW,R_0603_1608Metric,SMD,LCSC,C23163,https://www.lcsc.com/product-detail/Chip-span-style-backgrou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
16,"R2, R3, R6, R7",4,YAGEO,RC0603JR-0710KL,10K,Resistor 10K 5% 100mW,R_0603_1608Metric,SMD,LCSC,C99198,https://www.lcsc.com/product-detail/_YAGEO-_C99198.html
17,R4,1,UNI-ROYAL(Uniroyal Elec),0603WAF1005T5E,10M,Resistor 10M 1% 100mW,R_0603_1608Metric,SMD,LCSC,C7250,https://www.lcsc.com/product-detail/Chip-span-style-backgrou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
18,"R5, R12, R13",3,FOJAN,FRC0603J102TS,1K,Resistor 1K 5% 100mW,R_0603_1608Metric,SMD,LCSC,C2907113,https://www.lcsc.com/product-detail/_FOJAN-_C2907113.html
19,"R8, R9",2,UNI-ROYAL(Uniroyal Elec),0603WAJ0105T5E,1M,Resistor 1M 5% 100mW,R_0603_1608Metric,SMD,LCSC,C26098,https://www.lcsc.com/product-detail/Chip-span-style-backgrou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
20,"SC1, SC2, SC3, SC4",4,ANYSOLAR Ltd,KXOB25-05X3F,KXOB25-05X3F,Monocrystalline Solar Cell 30.7 mW 2.07 V,KXOB25-05X3F,SMD,Digikey,KXOB25-05X3FCT-ND,https://www.digikey.com/en/products/detail/anysolar-ltd/KXOB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
21,SW3,1,E-Switch,TL3342F160QG,RESET,SPST SMD Tactile Switches,SW_SPST_TL3342,SMD,LCSC,C2886898,https://www.lcsc.com/product-detail/Tactile-Switches_E-Switc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
22,SW4,1,E-Switch,TL3342F160QG,BOOT,SPST SMD Tactile Switches,SW_SPST_TL3342,SMD,LCSC,C2886898,https://www.lcsc.com/product-detail/Tactile-Switches_E-Switc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
23,U1,1,Bosch Sensortec,BME688,BME688,"Air Quality Sensors Combined gas, humidity, pressure and temperature sensor",BME688,SMD,Mouser,262-BME688,https://www.mouser.com/ProductDetail/Bosch-Sensortec/BME688?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
24,U2,1,RAKwireless,309054,RAK3172-T,"RAK3172-T Module with TCXO, without IPEX, Frequency 915MHz, Band AS923 ",RAK3172,SMD,RAKwireless,309054,Contact inquiry@rakwireless.com for SKU: 309054
25,U3,1,e-peas,AEM10941-QFN,AEM10941,Photovoltaic Energy Harvesting Manager,QFN-28-1EP_5x5mm_P0.5mm_EP3.35x3.35mm,SMD,Mouser,120-AEM10941-QFN,https://www.mouser.com/ProductDetail/e-peas/AEM10941-QFN?qs=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
26,U4,1,Torex Semicon,XC6215B332MR-G,XC6215,Linear Voltage Regulators (LDO) 200mA Fixed +3.3V,SOT-23-5,SMD,LCSC,C98230,https://www.lcsc.com/product-detail/Linear-Voltage-Regulator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
27,"C15, C16",0,-,-,DNP,Do Not Populate,-,DNP,-,-,-

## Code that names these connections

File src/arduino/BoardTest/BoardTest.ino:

#define LED0          PA15
#define LED1          PA1
#define POWER_STATUS  PB12
#define BATT_MEASURE  PB3

#define ADC_TO_BATTERY  0.00118042553

void setup() {
  Serial.begin(115200);
  
  pinMode( BATT_MEASURE, INPUT );
  pinMode( POWER_STATUS, INPUT );
  pinMode( LED0, INPUT );
  pinMode( LED1, INPUT );
  analogReadResolution( 12 );
}

void loop() {
  digitalWrite(LED0, LOW);  
  digitalWrite(LED1, HIGH);
  delay(500);
  digitalWrite(LED0, HIGH);
  digitalWrite(LED1, LOW);
  delay(500);

  int   batt_measure_adc  = analogRead( BATT_MEASURE );
  float batt_measure_volt = batt_measure_adc * ADC_TO_BATTERY;
  Serial.printf("Battery Voltage ADC: %d, Battery Voltage: %f\n", batt_measure_adc, batt_measure_volt);
  delay(100);
}

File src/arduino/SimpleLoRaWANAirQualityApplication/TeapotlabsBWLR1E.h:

#ifndef TEAPOTLABS_BWLR1E_H
#define TEAPOTLABS_BWLR1E_H

#include "Arduino.h"
#include "Zanshin_BME680.h"

// configuration for teapot bwlr3d application
#include "TeapotlabsBWLR1EConfig.h"

/* pin definition */
#define RED_LED               PA15
#define GREEN_LED             PA1
#define POWER_STATUS          PB12
#define I2C_SDA               PA11
#define I2C_SCL               PA12
#define BATT_MEASURE          PB3

#ifndef ADC_TO_BATTERY
  #error "ADC_TO_BATTERY not set"
#endif

/* application definition */
namespace teapotlabs{
namespace bwlr1e {
  enum class ReturnCode {
    kOk = 0,
    kError,
    kBme68xNotFound,
    kInvalidLed,
    kPeripheralOff,
    kBme68xReadFail,
    kTimeout,
  };
  
  enum class Led {
    kGreen = 0,
    kRed,
  };

  class Application {
    private:
      BME680_Class      bme68x;
    
      void  SetupBme68x();
    public:
      Application();
      void          Initialize();
      ReturnCode    ConfigureSensor();

      /**
       * Enable or disable LED
       *
       * @param led target led Target HDOP value
       * @param enable enable or disable led
       * @return `kOk` if successfully set LED
       */
      ReturnCode    EnableLed( Led led, bool enable );
      int           ReadBatteryAdc();
      float         ReadBatteryVoltage();
      bool          ReadPowerStatus();
      ReturnCode    GetEnvironmentalData( float& temperature, float& humidity, float& pressure );
      void          BlinkLedIndicator( uint32_t ms );
      void          BlinkLedIndicator(Led led, uint32_t ms);
      void          BlinkLedIndicator(Led led, int total_blink, uint32_t ms);
  };
  
} // namespace bwlr3d 
} // namespace teapotlabs

#endif

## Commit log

2022-08-04 revision 1
2022-08-06 revision 2
2022-08-22 add documents directory
2022-08-22 revision 3
2022-08-22 add arduino source code example
2022-08-22 adddesign artifacts
2022-08-22 move images to docs/images
2022-08-22 crop docs images
2022-08-22 add aux images
2022-08-22 add readme
2022-08-22 rename image
2022-08-22 remove old image
2022-08-22 add kicad library
2022-08-23 rename license file
2022-08-25 update logo
2022-09-03 update library
2022-09-03 update footprint and library
2022-09-26 move battery measurement to PB3
2022-10-22 change jst type to smt
2022-10-22 add revision 4 rc1 gerber.zip
2023-08-09 improve layout and silkscreen info
2023-08-09 added qwiic connector
2023-08-09 add qwiic silkscreen info
2023-08-09 improve qwiic sda trace
2023-08-11 improve silkscreen graphic and wiring
2023-08-11 add gnd vias
2023-08-11 rename value unit of components
2023-08-12 fix led polarity and minor wiring changes
2023-08-12 change library to project-level and minor changes
2023-08-12 update library to project-level
2023-08-12 small improvement and add production info
2023-08-13 update RAK3172 description
2023-08-13 update components rotation
2023-08-13 minor description changes
2023-08-13 update bill of materials
2023-08-13 update solar footprint
2023-08-13 initial production files
2023-08-18 rotate components
2023-08-18 add production files
2023-08-18 rotate BT1
2023-09-07 initial programmer
2023-09-07 fix filter cap footprint
2023-09-07 update page title
2023-09-07 fix components value
2023-09-07 add usb-c receptacle
2023-09-07 fix incorrect resistor desc
2023-09-07 rename value
2023-09-07 re-annotate
2023-09-07 add production file
2023-09-07 clean-up
2023-09-07 change folder structure
2023-09-07 update footprint library
2023-09-09 update component value
2023-09-09 move batt jst to top and change to rev 2
2023-09-21 improve usb diff pair and change to rev 3
2023-09-26 change csrc aem10941 to 10uf
2023-10-02 update better solar cell models
2023-10-02 update 3d model file
2023-10-02 update 3d model
2023-10-08 add 3d case
2023-10-08 updated documentation
2023-10-09 update documentation
2023-10-09 update doc files
2023-10-09 update src
2023-10-09 code example update
2023-10-10 update power save
2023-10-10 update code
2023-10-10 code update
2023-10-12 add environtmental code example
2023-10-14 update doc
2023-10-14 update docs
2023-10-17 add marker for pcb blender export
2023-10-24 add programmer images
2023-10-24 add showcase render
2023-10-26 update programmer readme
2023-10-26 readme.md
2023-12-06 mbedos example
2023-12-07 update deep-sleep
2023-12-07 update submodule
2023-12-07 update lib
2023-12-07 update mbed-os sdk
2023-12-07 update lib url
2023-12-08 update compile-able example
2023-12-08 remove submodule, let mbedos take care it
2023-12-09 update simplified bme688 test
2023-12-11 add test-flash
2023-12-12 update test flash and deep-sleep
2023-12-12 update bsec bme688
2023-12-13 clean-up bsec code and add defer
2023-12-14 first successful measurement with sleep
2023-12-14 update library interface
2023-12-16 initial effort to re-implement arduino library
2023-12-19 wip: proper bsec implementation
2023-12-19 add ArrayPointer class
2023-12-19 revert using ArrayPointer
2023-12-20 code clean-up
2023-12-22 initial implementation for bsec2 arduino
2023-12-22 add correct timer calls
2023-12-23 first working air quality with sleep
2023-12-29 Change from ssh to https for lib cloning
2023-12-30 clean-up add chip id read
2023-12-30 namespace clean-up and implement GetChipId
2023-12-30 clean-up static definition
2023-12-30 namespace clean-up
2023-12-30 add co2 and compensated temp, humid
2023-12-30 comment clean-up
2023-12-31 add correct antenna power switch and crystal configuration
2024-01-03 test-lorawan initial commit based on https://github.com/ARMmbed/mbed-os-example-lorawan
2025-04-29 initial air quality app

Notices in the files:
readme.md:
License:
License: MIT
